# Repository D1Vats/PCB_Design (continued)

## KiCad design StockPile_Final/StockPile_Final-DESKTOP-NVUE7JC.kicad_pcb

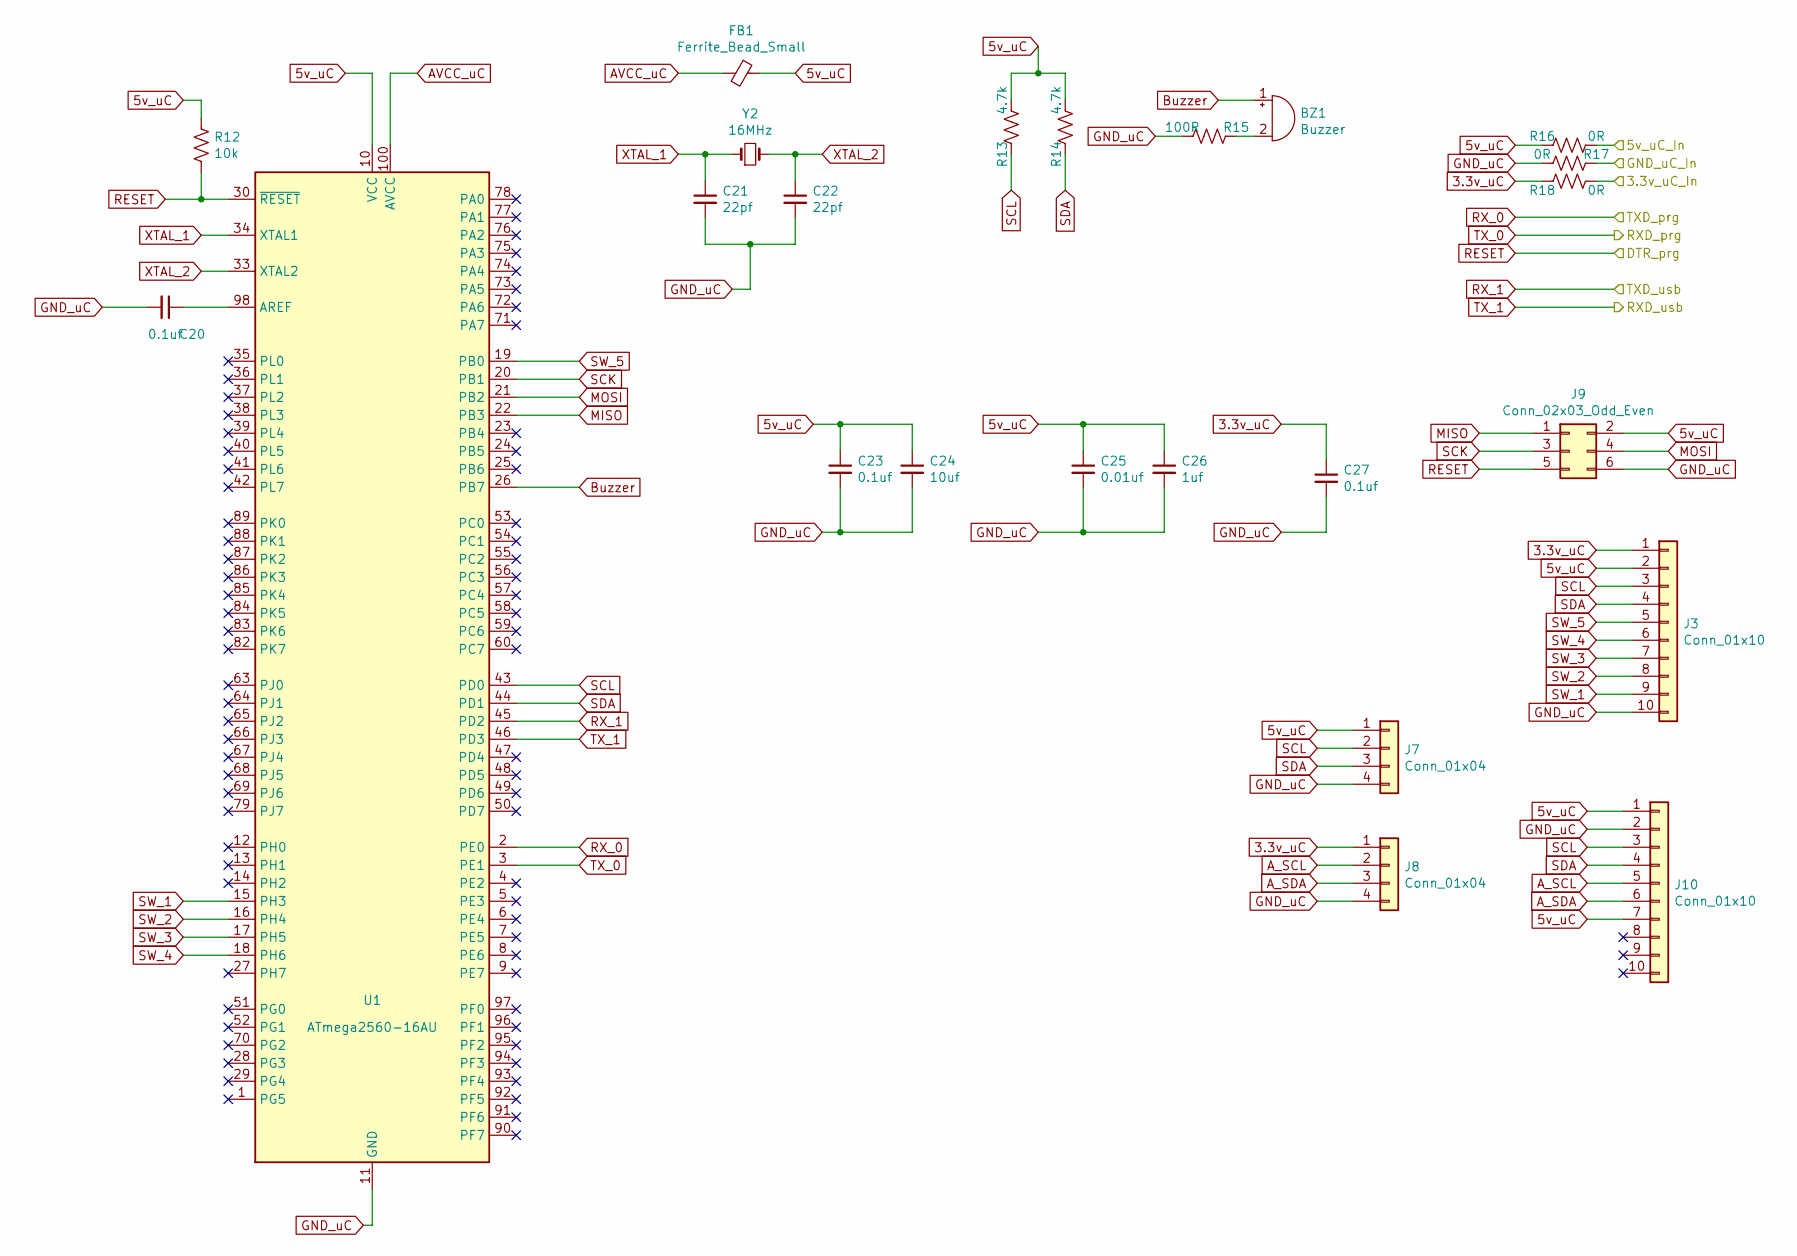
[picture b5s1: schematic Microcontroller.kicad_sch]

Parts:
BZ1: Buzzer; Buzzer_12x9.5RM7.6
C20, C23, C27: 0.1uf; C_0805_2012Metric
C21, C22: 22pf; C_0805_2012Metric
C24: 10uf; C_0805_2012Metric
C25: 0.01uf; C_0805_2012Metric
C26: 1uf; C_0805_2012Metric
FB1: Ferrite_Bead_Small; L_0805_2012Metric
J3, J10: Conn_01x10; JST_XH_B10B-XH-AM_1x10_P2.50mm_Vertical
J7, J8: Conn_01x04; PinSocket_1x04_P2.54mm_Horizontal
J9: Conn_02x03_Odd_Even; PinSocket_2x03_P2.54mm_Vertical
R12: 10k; R_0805_2012Metric
R13, R14: 4.7k; R_0805_2012Metric
R15: 100R; R_0805_2012Metric
R16, R17, R18: 0R; R_0805_2012Metric
U1: ATmega2560-16AU; TQFP-100_14x14mm_P0.5mm
Y2: 16MHz; Crystal_HC49-4H_Vertical

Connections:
3.3V: R18.1; also elsewhere on the board
3.3v_uC: C27.1, J3.1, J8.1, R18.2; also elsewhere on the board
5V: R16.1; also elsewhere on the board
5v_uC: C23.1, C24.1, C25.1, C26.1, FB1.1, J3.2, J7.1, J9.2, J10.1, J10.7, R12.1, R13.1, R14.2, R16.2, U1.10 (VCC), U1.31 (VCC), U1.61 (VCC), U1.80 (VCC); also elsewhere on the board
AVCC_uC: FB1.2, U1.100 (AVCC)
Buzzer: BZ1.1 (-), U1.26 (PB7)
DTR_prg: J9.5, R12.2, U1.30 (~RESET); also elsewhere on the board
GND_USB: R17.2; also elsewhere on the board
GND_uC: C20.2, C21.2, C22.2, C23.2, C24.2, C25.2, C26.2, C27.2, J3.10, J7.4, J8.4, J9.6, J10.2, R15.1, R17.1, U1.11 (GND), U1.32 (GND), U1.62 (GND), U1.81 (GND), U1.99 (GND); also elsewhere on the board
MISO: J9.1, U1.22 (PB3)
MOSI: J9.4, U1.21 (PB2)
unnamed: BZ1.2 (+), R15.2
unnamed: C20.1, U1.98 (AREF)
unnamed: J8.2, J10.5
unnamed: J8.3, J10.6
RXD1_usb: U1.46 (PD3); also elsewhere on the board
RXD_prg: U1.3 (PE1); also elsewhere on the board
RX_0: U1.2 (PE0); also elsewhere on the board
RX_1: U1.45 (PD2); also elsewhere on the board
SCK: J9.3, U1.20 (PB1)
SCL: J3.3, J7.2, J10.3, R13.2, U1.43 (PD0); also elsewhere on the board
SDA: J3.4, J7.3, J10.4, R14.1, U1.44 (PD1); also elsewhere on the board
SW_1: J3.9, U1.15 (PH3)
SW_2: J3.8, U1.16 (PH4)
SW_3: J3.7, U1.17 (PH5)
SW_4: J3.6, U1.18 (PH6)
SW_5: J3.5, U1.19 (PB0)
XTAL_1: C21.1, U1.34 (XTAL1), Y2.1
XTAL_2: C22.1, U1.33 (XTAL2), Y2.2

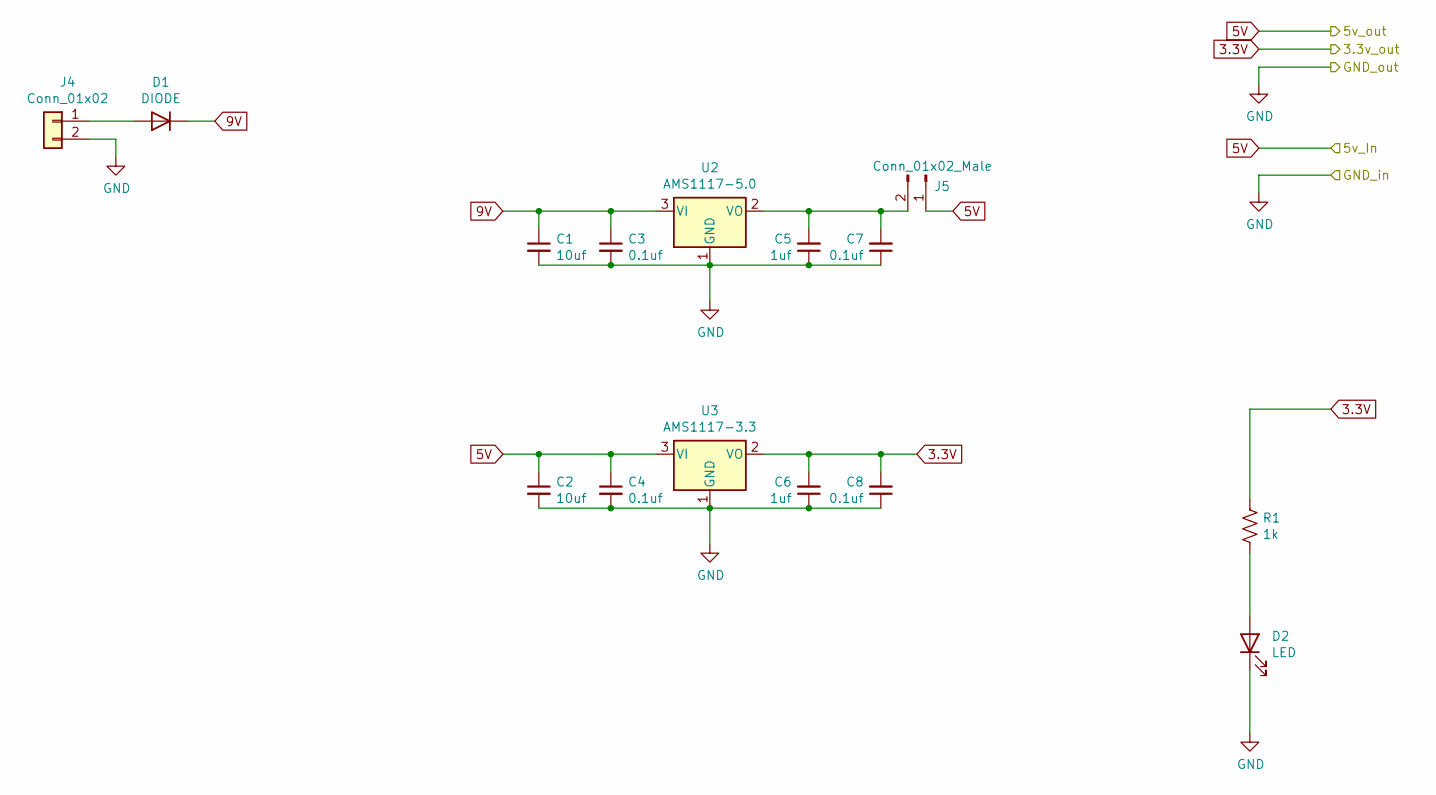
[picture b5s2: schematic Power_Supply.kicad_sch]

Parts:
C1, C2: 10uf; C_0805_2012Metric
C3, C4, C7, C8: 0.1uf; C_0805_2012Metric
C5, C6: 1uf; C_0805_2012Metric
D1: DIODE; D_SOD-323_HandSoldering
D2: LED; LED_0805_2012Metric
J4: Conn_01x02; JST_XH_B2B-XH-AM_1x02_P2.50mm_Vertical
J5: Conn_01x02_Male; PinSocket_1x02_P2.54mm_Vertical
R1: 1k; R_0805_2012Metric
U2: AMS1117-5.0; SOT-223-3_TabPin2
U3: AMS1117-3.3; SOT-223-3_TabPin2

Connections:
3.3V: C6.2, C8.2, R1.1, U3.2 (VO); also elsewhere on the board
5V: C2.1, C4.1, J5.1, U3.3 (VI); also elsewhere on the board
9V: C1.1, C3.1, D1.2 (K), U2.3 (VI)
GND_USB: C1.2, C2.2, C3.2, C4.2, C5.1, C6.1, C7.1, C8.1, D2.1 (K), J4.2, U2.1 (GND), U3.1 (GND); also elsewhere on the board
unnamed 20: C5.2, C7.2, J5.2, U2.2 (VO); also elsewhere on the board
unnamed: D1.1 (A), J4.1
unnamed: D2.2 (A), R1.2

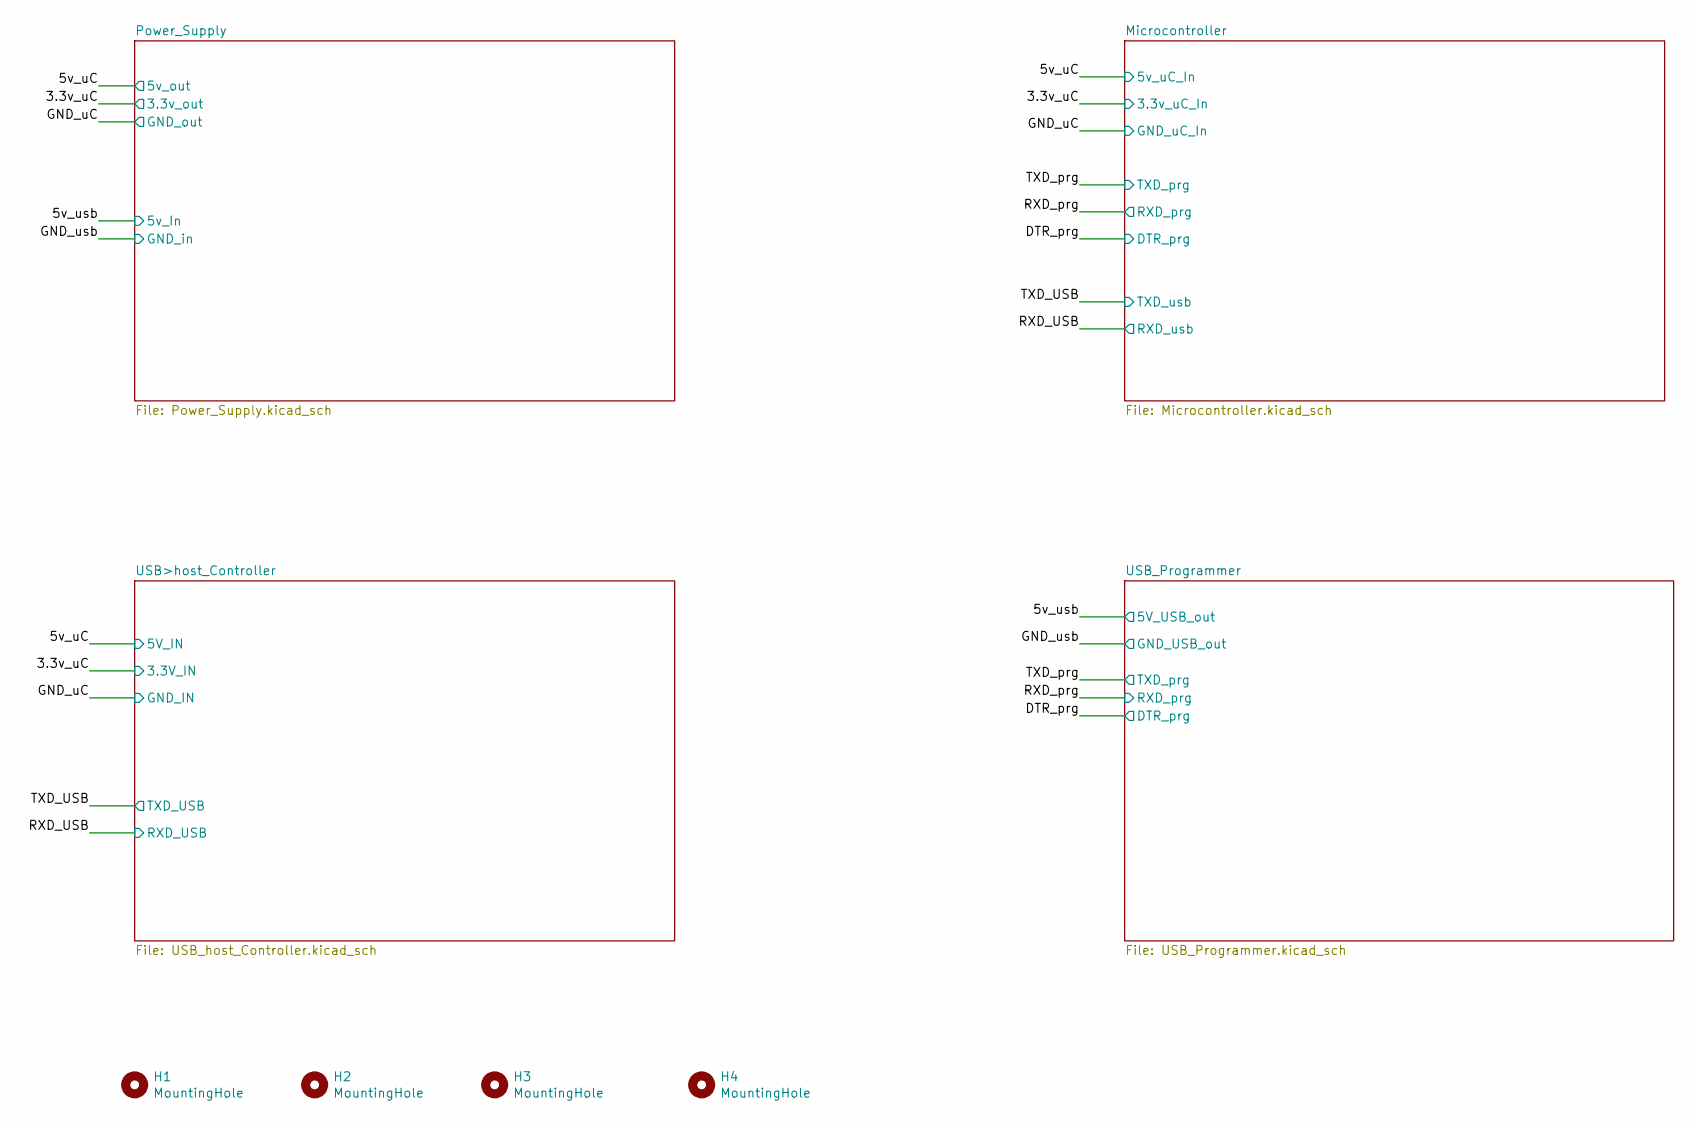
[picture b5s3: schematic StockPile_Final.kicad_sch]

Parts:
H1, H2, H3, H4: MountingHole; MountingHole_3.2mm_M3

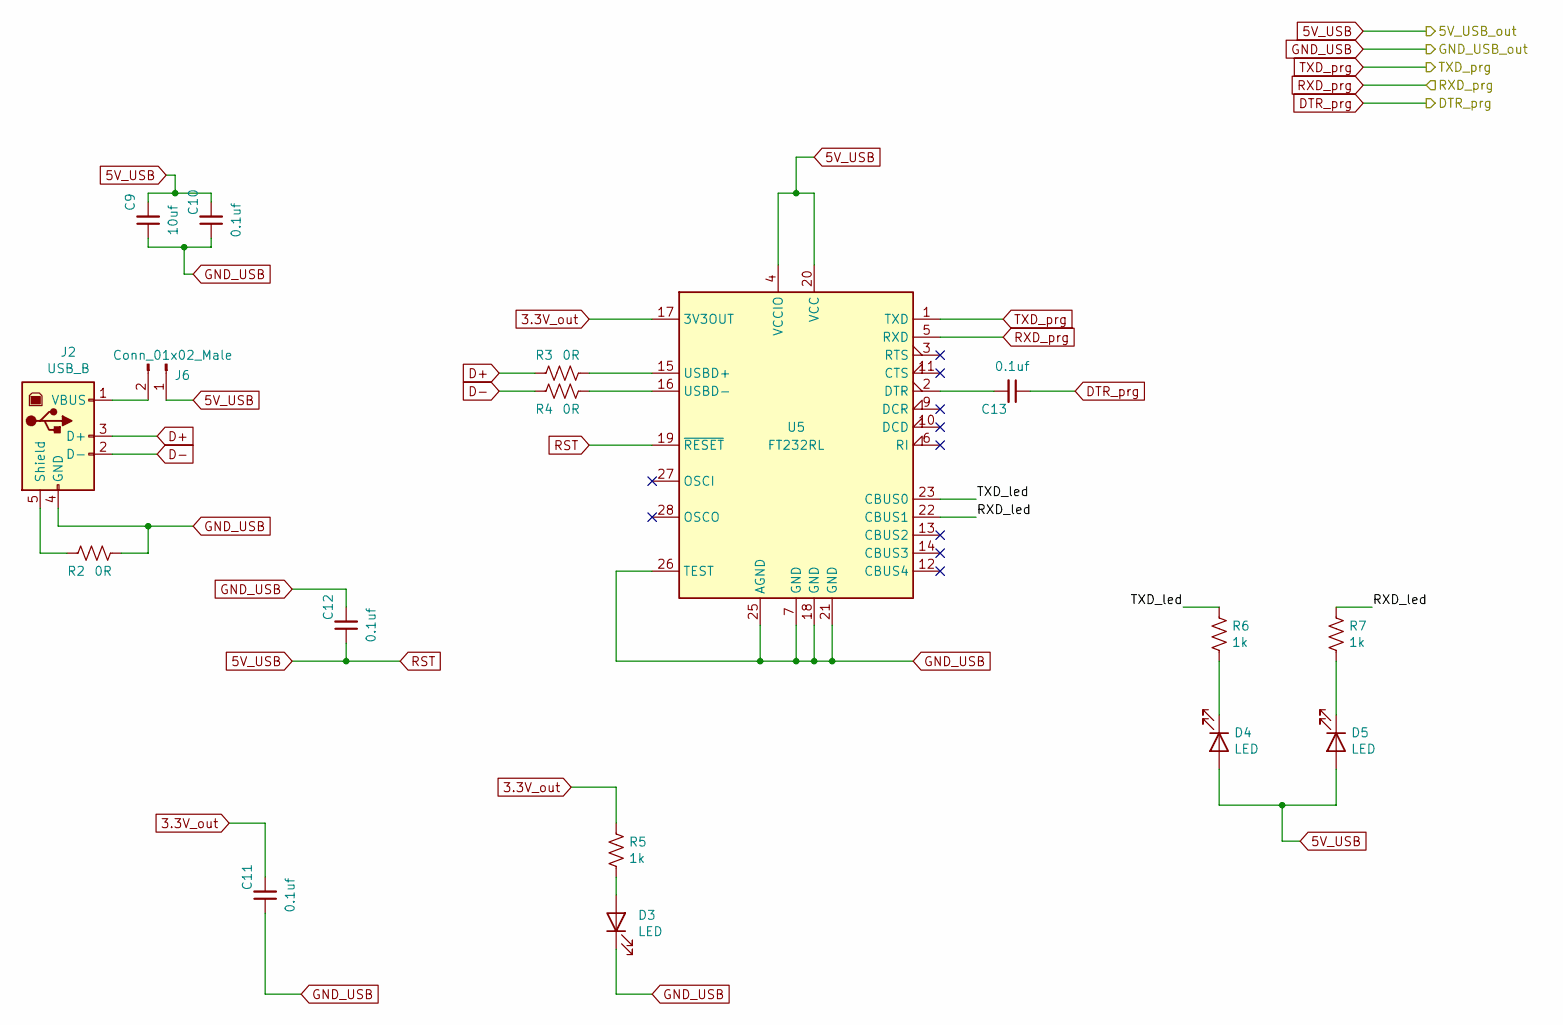
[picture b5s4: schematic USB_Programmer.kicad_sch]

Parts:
C9: 10uf; C_0805_2012Metric
C10, C11, C12, C13: 0.1uf; C_0805_2012Metric
D3, D4, D5: LED; LED_0805_2012Metric
J2: USB_B; USB_B_OST_USB-B1HSxx_Horizontal
J6: Conn_01x02_Male; PinSocket_1x02_P2.54mm_Vertical
R2, R3, R4: 0R; R_0805_2012Metric
R5, R6, R7: 1k; R_0805_2012Metric
U5: FT232RL; SSOP-28_5.3x10.2mm_P0.65mm

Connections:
3.3V_out: C11.2, R5.1, U5.17 (3V3OUT)
5V: C9.2, C10.2, C12.1, D4.2 (A), D5.2 (A), J6.1, U5.4 (VCCIO), U5.19 (~RESET), U5.20 (VCC); also elsewhere on the board
/USB_Programmer/RXD_led: R7.1, U5.22 (CBUS1)
/USB_Programmer/TXD_led: R6.1, U5.23 (CBUS0)
D+: J2.3 (D+), R3.2; also elsewhere on the board
D-: J2.2 (D-), R4.2; also elsewhere on the board
DTR_prg: C13.1; also elsewhere on the board
GND_USB: C9.1, C10.1, C11.1, C12.2, D3.1 (K), J2.4 (GND), R2.1, U5.7 (GND), U5.18 (GND), U5.21 (GND), U5.25 (AGND), U5.26 (TEST); also elsewhere on the board
unnamed: C13.2, U5.2 (DTR)
unnamed: D3.2 (A), R5.2
unnamed: D4.1 (K), R6.2
unnamed: D5.1 (K), R7.2
unnamed 32: J2.1 (VBUS), J6.2; also elsewhere on the board
unnamed 33: J2.5 (Shield), R2.2; also elsewhere on the board
unnamed: R3.1, U5.15 (USBD+)
unnamed: R4.1, U5.16 (USBD-)
RXD_prg: U5.5 (RXD); also elsewhere on the board
RX_0: U5.1 (TXD); also elsewhere on the board

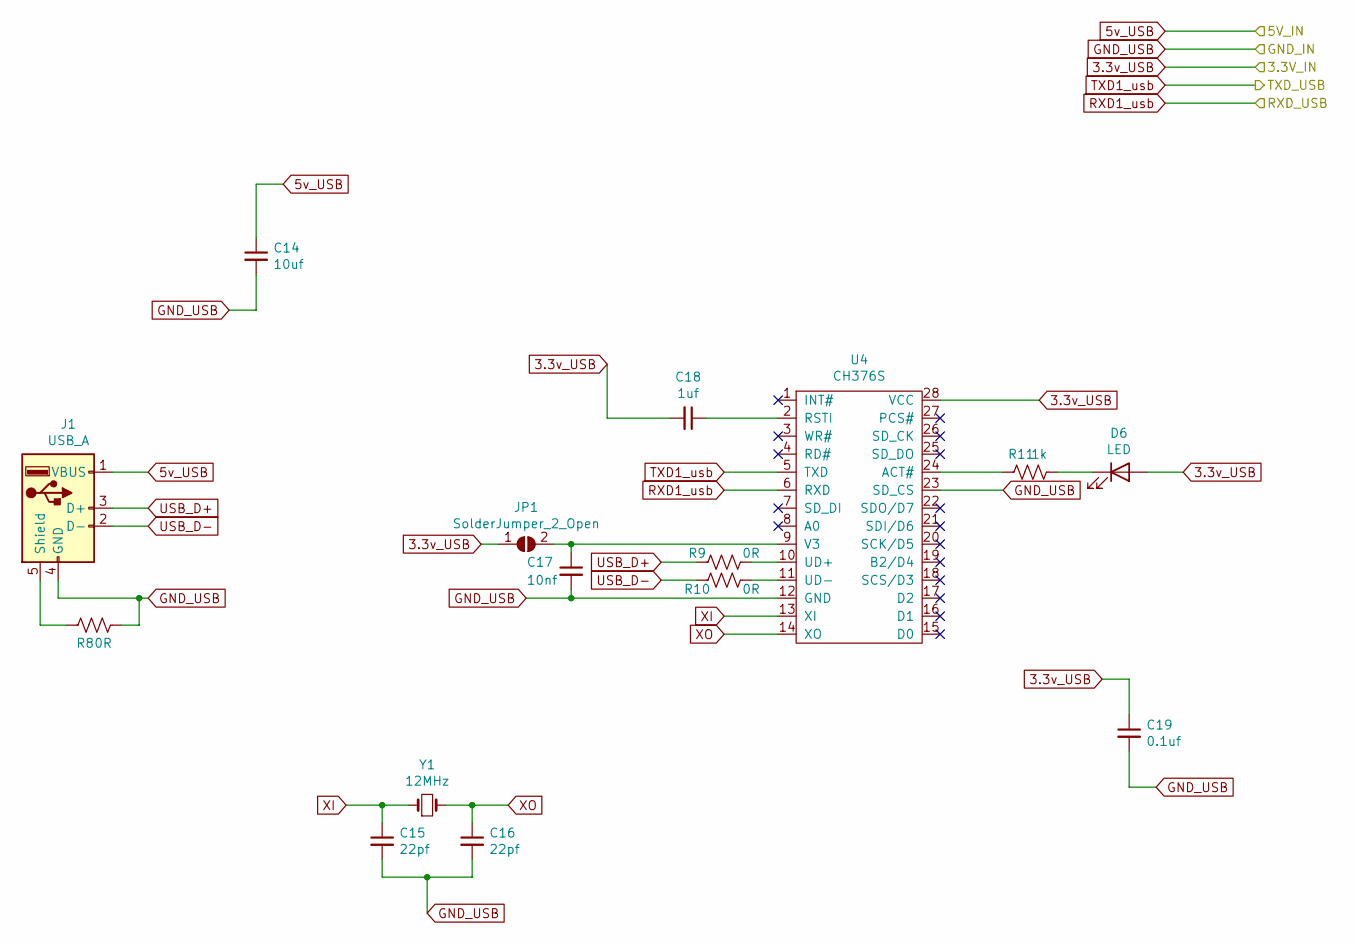
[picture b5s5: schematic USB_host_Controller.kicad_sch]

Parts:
C14: 10uf; C_0805_2012Metric
C15, C16: 22pf; C_0805_2012Metric
C17: 10nf; C_0805_2012Metric
C18: 1uf; C_0805_2012Metric
C19: 0.1uf; C_0805_2012Metric
D6: LED; LED_0805_2012Metric
J1: USB_A; USB_A_Molex_67643_Horizontal
JP1: SolderJumper_2_Open; SolderJumper-2_P1.3mm_Open_RoundedPad1.0x1.5mm
R8, R9, R10: 0R; R_0805_2012Metric
R11: 1k; R_0805_2012Metric
U4: CH376S; SOIC-28W_7.5x17.9mm_P1.27mm
Y1: 12MHz; Crystal_HC49-4H_Vertical

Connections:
3.3V: C18.2, C19.1, D6.2 (A), JP1.1 (A), U4.28 (VCC); also elsewhere on the board
5V: C14.1, J1.1 (VBUS); also elsewhere on the board
GND_USB: C14.2, C15.2, C16.2, C17.2, C19.2, J1.4 (GND), R8.1, U4.12 (GND), U4.23 (SD_CS); also elsewhere on the board
unnamed: C17.1, JP1.2 (B), U4.9 (V3)
unnamed: C18.1, U4.2 (RSTI)
unnamed: D6.1 (K), R11.1
unnamed: J1.5 (Shield), R8.2
unnamed: R9.1, U4.10 (UD+)
unnamed: R10.1, U4.11 (UD-)
unnamed: R11.2, U4.24 (ACT#)
RXD1_usb: U4.6 (RXD); also elsewhere on the board
RX_1: U4.5 (TXD); also elsewhere on the board
USB_D+: J1.3 (D+), R9.2
USB_D-: J1.2 (D-), R10.2
XI: C15.1, U4.13 (XI), Y1.1
XO: C16.1, U4.14 (XO), Y1.2

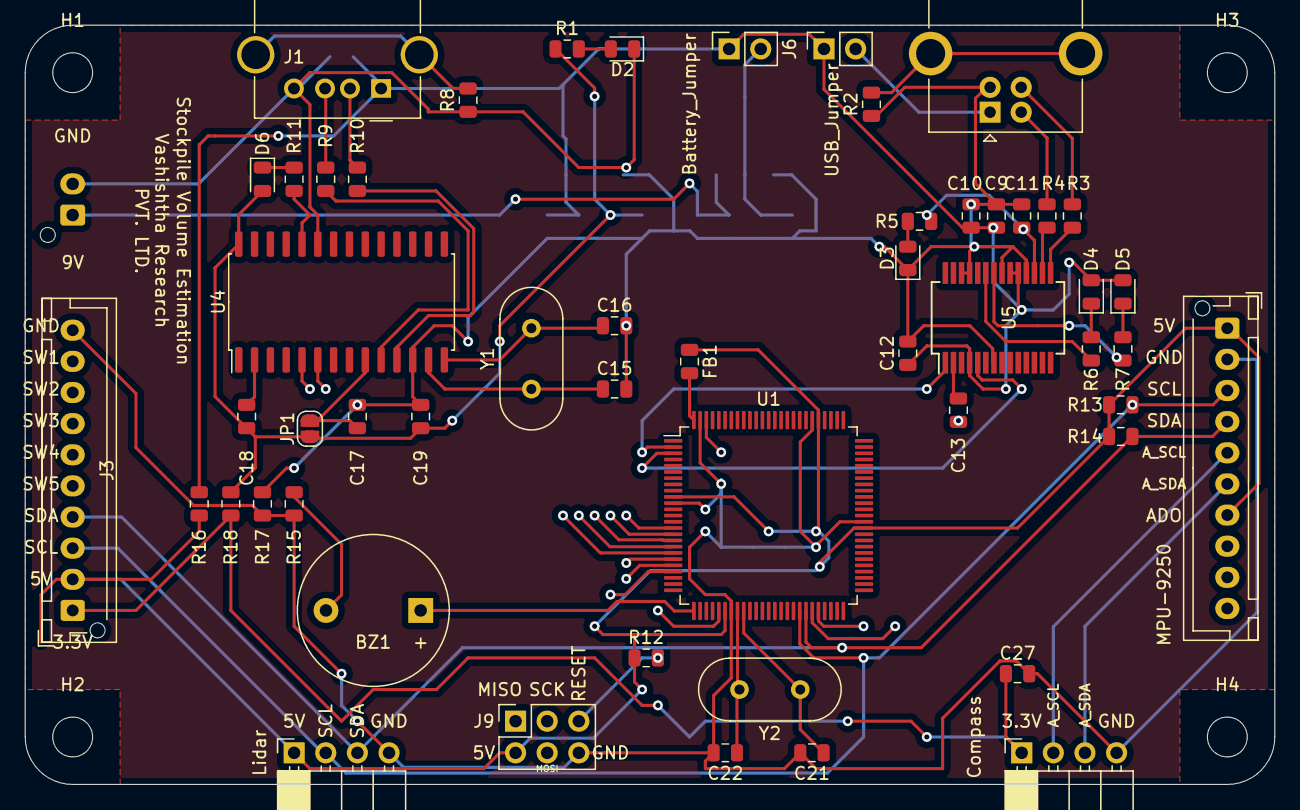
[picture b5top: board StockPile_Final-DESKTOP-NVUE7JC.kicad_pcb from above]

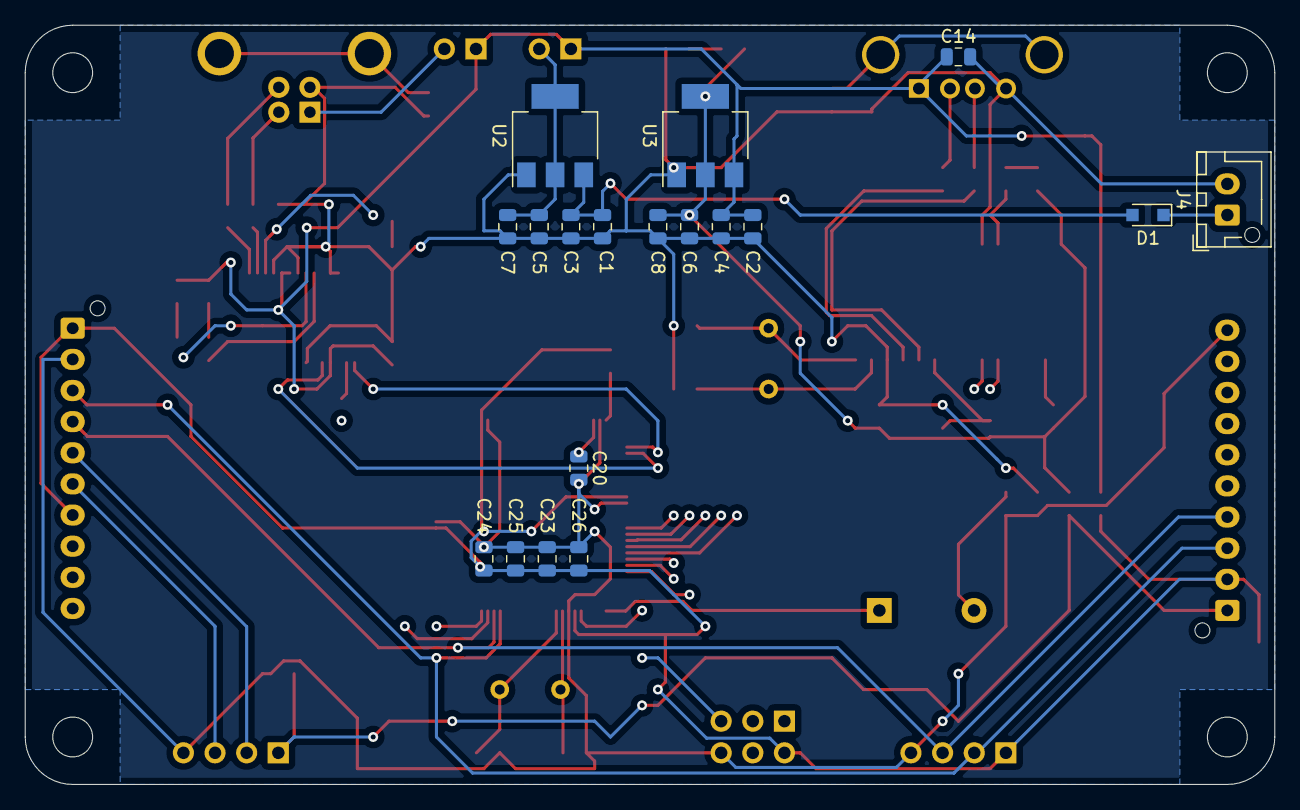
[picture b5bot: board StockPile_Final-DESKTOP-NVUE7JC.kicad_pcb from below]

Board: 4 copper layers, 100.3 x 61.0 mm, 75 parts (18 on the bottom side), 57 nets.

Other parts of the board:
Battery_Jumper: Conn_01x02_Male; PinSocket_1x02_P2.54mm_Vertical
Compass: Conn_01x04; PinSocket_1x04_P2.54mm_Horizontal
Lidar: Conn_01x04; PinSocket_1x04_P2.54mm_Horizontal
MPU-9250: Conn_01x10; JST_XH_B10B-XH-AM_1x10_P2.50mm_Vertical
USB_Jumper: USB_B; USB_B_OST_USB-B1HSxx_Horizontal

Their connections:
3.3v_uC: Compass.1; also elsewhere on the board
5V: Battery_Jumper.1; also elsewhere on the board
5v_uC: Lidar.1, MPU-9250.1, MPU-9250.7; also elsewhere on the board
A_SCL: Compass.2, MPU-9250.5
A_SDA: Compass.3, MPU-9250.6
D+: USB_Jumper.3; also elsewhere on the board
D-: USB_Jumper.2; also elsewhere on the board
GND_USB: USB_Jumper.4; also elsewhere on the board
GND_uC: Compass.4, Lidar.4, MPU-9250.2; also elsewhere on the board
unnamed 20: Battery_Jumper.2; also elsewhere on the board
unnamed 32: USB_Jumper.1; also elsewhere on the board
unnamed 33: USB_Jumper.5; also elsewhere on the board
SCL: Lidar.2, MPU-9250.3; also elsewhere on the board
SDA: Lidar.3, MPU-9250.4; also elsewhere on the board
